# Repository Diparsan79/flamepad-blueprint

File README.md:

# FLAMExPAD 🔥

**BUILT TO LAST.**

FLAMExPAD is a minimal 4-key macropad powered by [KMK](http://kmk.fyi) firmware on a Seeeduino XIAO (SAMD21). It features 2 SK6812MINI-E RGB LEDs, a clean 2-layer keymap with Spotlight macros for launching apps, and a compact direct-wired design — no diodes, no encoder, no display. Just keys that *do things*.

Built for the [Hackpad Blueprint](https://hackpad.hackclub.com/) YSWS by Hack Club.

---

## Features
- 🔥 4 Cherry MX mechanical keys — direct wired, no diodes needed
- 💡 2x SK6812MINI-E RGB LEDs — daisy-chained underglow
- 🧠 [KMK Firmware](http://kmk.fyi) on CircuitPython — fully hardcoded, no companion app
- 🔀 2 Layers — tap/hold layer switching on K4
- 🚀 Spotlight macros — launch Photo Booth, Spotify, VS Code, and Brave instantly
- 🔌 USB powered — plug and go

---

## Keymap

### Layer 0 (Default)

| Key | Action |
|-----|--------|
| **K1** | `Ctrl + `` ` |
| **K2** | `F5` |
| **K3** | Macro: Open **Photo Booth** via Spotlight |
| **K4** | Tap: `Cmd+S` · Hold: Momentary Layer 1 |

### Layer 1 (Momentary — hold K4)

| Key | Action |
|-----|--------|
| **K1** | Macro: Open **Spotify** via Spotlight |
| **K2** | Macro: Open **Visual Studio Code** via Spotlight |
| **K3** | Macro: Open **Brave** via Spotlight |
| **K4** | Transparent (layer hold passes through) |

> All macros follow the pattern: `Cmd+Space` → 200ms delay → type app name → 150ms delay → `Enter`

---

## PCB

The PCB was designed in **KiCad**. Direct wiring to the Seeeduino XIAO — no key matrix, no diodes. The two SK6812MINI-E LEDs are daisy-chained from pin D9.

**Schematic**

**PCB Render**

### Pin Assignments

| Component | XIAO Pin | GPIO |
|-----------|----------|------|
| SW1 | Pin 1 | D0 (PA02) |
| SW2 | Pin 2 | D1 (PA4) |
| SW3 | Pin 3 | D2 (PA10) |
| SW4 | Pin 5 | D4 (PA8) |
| LED Data (D1 DIN) | Pin 10 | D9 (PA5) |
| LED D1 DOUT → D2 DIN | Daisy-chained | — |
| LED VDD | 5V | — |
| LED VSS | GND | — |

---

## CAD Model

The case was designed in **Fusion 360**. Two-part design: a top plate and a bottom enclosure.

---

## Firmware Overview

FLAMExPAD runs [KMK](http://kmk.fyi) firmware on CircuitPython. Everything is hardcoded — no VIA, no companion app.

- **Framework:** KMK (CircuitPython-based keyboard firmware)
- **Board:** Seeeduino XIAO (SAMD21)
- **Layers:** 2 (momentary switching via hold on K4)
- **Macros:** Spotlight-based app launchers with configurable delays
- **RGB:** Static color on 2 daisy-chained SK6812MINI-E LEDs

### File Structure

```
firmware/
├── boot.py     # USB HID device configuration
├── kb.py       # Hardware definition (pins, scanner, RGB pin)
└── main.py     # Keymap, layers, macros, RGB config
```

### Setup Instructions

1. **Flash CircuitPython** onto your Seeeduino XIAO (SAMD21) from [circuitpython.org](https://circuitpython.org/board/seeeduino_xiao/)
2. Copy the **`kmk/`** folder from [KMKfw/kmk_firmware](https://github.com/KMKfw/kmk_firmware) to the root of your `CIRCUITPY` drive
3. Copy **`neopixel.mpy`** from the [CircuitPython library bundle](https://circuitpython.org/libraries) into `CIRCUITPY/lib/`
4. Copy `boot.py`, `kb.py`, and `main.py` from the `firmware/` folder to the root of `CIRCUITPY`
5. Unplug and replug — you're done! 🔥

---

## BOM

| Qty | Component |
|-----|-----------|
| 4x | Cherry MX Switches |
| 4x | Blank DSA Keycaps |
| 2x | SK6812MINI-E RGB LEDs |
| 1x | Seeeduino XIAO (SAMD21) |
| 1x | Custom PCB |
| 1x | Case (2 parts — 3D printed in Fusion 360) |

---

## Fun Facts & Lessons Learned 🧠

- 🔄 Changed the **entire build three times** because I had no idea what half the components were actually for. Trial by fire (fitting for FLAMExPAD).
- 🌅 Started on **March 2nd morning**, finished at **March 3rd, 2 AM**. One long session.
- 📅 First attempt at Blueprint was back in **December** — but it was way too overwhelming at first. Came back stronger.
- 🔮 **Future plans:** More firmware layers, maybe an encoder or OLED in v2. The foundation is solid.

> "If at first you don't succeed, redesign it three more times." — Me, probably at 1 AM

---

## Credits & Resources

- [KMK Firmware](https://github.com/KMKfw/kmk_firmware) — The CircuitPython keyboard framework
- [Orpheuspad](https://github.com/hackclub/hackpad/tree/main/hackpads/orpheuspad) — The reference hackpad that inspired this build
- [Hack Club Hackpad](https://hackpad.hackclub.com/) — The YSWS that started it all
- [CircuitPython](https://circuitpython.org/) — The Python runtime for microcontrollers
- [KiCad](https://www.kicad.org/) — PCB design
- [Fusion 360](https://www.autodesk.com/products/fusion-360/) — Case CAD design

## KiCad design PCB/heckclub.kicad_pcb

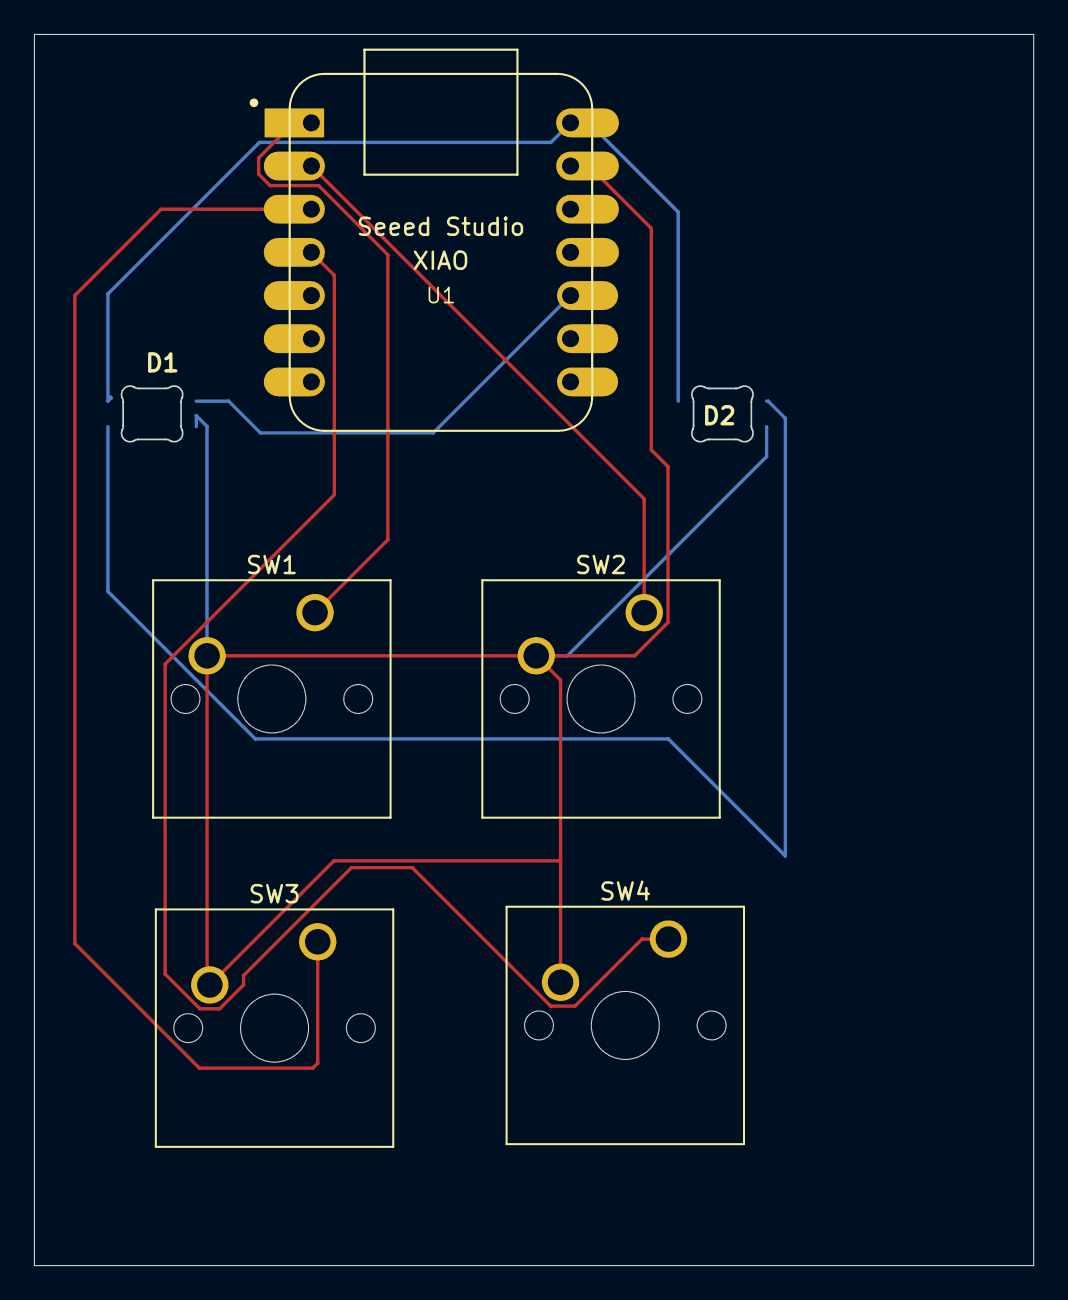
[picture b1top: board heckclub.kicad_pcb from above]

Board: 2 copper layers, 58.8 x 72.4 mm, 7 parts (0 on the bottom side), 8 nets.

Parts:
D1, D2: SK6812MINI-E; SK6812MINI-E_fixed
SW1, SW2, SW3, SW4: SW_Push; SW_Cherry_MX_1.00u_PCB
U1: SeeeduinoXIAO; XIAO-Generic-Hybrid-14P-2.54-21X17.8MM

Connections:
+5V: D1.1 (VDD), D2.1 (VDD), U1.14 (5V)
GND: D1.3 (VSS), D2.3 (VSS), SW1.2, SW2.2, SW3.2, SW4.2, U1.13 (GND)
unnamed: D1.4 (DIN), U1.10 (PA5_A9_D9_MISO)
unnamed: D1.2 (DOUT), D2.4 (DIN)
unnamed: SW1.1, U1.1 (PA02_A0_D0)
unnamed: SW2.1, U1.2 (PA4_A1_D1)
unnamed: SW3.1, U1.3 (PA10_A2_D2)
unnamed: SW4.1, U1.4 (PA11_A3_D3)

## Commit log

2026-03-02 too sleepy rn
2026-03-02 BLUEPRINTTTT
2026-03-02 imgs
2026-03-03 some immediate changes
